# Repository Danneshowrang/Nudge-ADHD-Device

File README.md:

# Nudge-ADHD-Device

## What is it
Nudge is a haptic feedback device made to combat ADHD-related time blindness. It does this by stimulating the user ever 15 minutes with a haptic effect.

## Why I made this project
I made this project because I, as an indivdual with ADHD who is heavily affected by time blindness, have missed a lot of opportunities, deadlines, and dates. (just now I missed the Stasis deadline to recieve a 150-point discount)
I hope that with this device, I, and others with ADHD, can create an artificial perception of time and live life with less regrets. 

## Future Plans
In the future I want to expand this device to not only be a Time-blindness solution, but an entire ADHD multitool. 
This means adding additional features such as calendar reminders, built-in focus timers, date countdowns, and a user-interactive display.

## Pictures

## CAD Link
Here is the link to the Onshape!
https://cad.onshape.com/documents/210c189d286efe197b4a566f/w/a50a3c19759326f033c6858b/e/ea3b0ad6e4c0592fd1c20846?renderMode=0&uiState=6a46bb6c4d6ed321eca43a19

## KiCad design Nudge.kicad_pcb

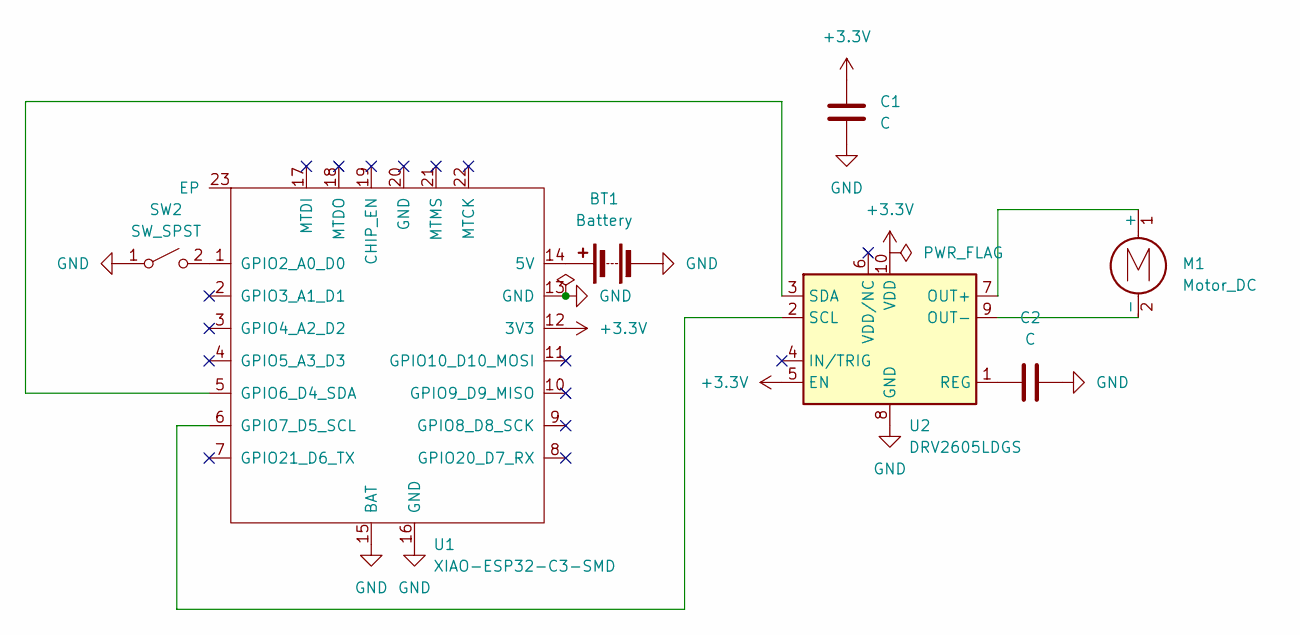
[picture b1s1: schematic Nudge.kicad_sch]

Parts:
BT1: Battery; SolderWire-0.5sqmm_1x02_P4.6mm_D0.9mm_OD2.1mm_Relief
C1, C2: C; C_0805_2012Metric
M1: Motor_DC; SolderWire-0.5sqmm_1x02_P4.6mm_D0.9mm_OD2.1mm_Relief
SW2: SW_SPST; SW_SPST_EVQP7A
U1: XIAO-ESP32-C3-SMD; MCU_Seeed_ESP32C3
U2: DRV2605LDGS; VSSOP-10_3x3mm_P0.5mm

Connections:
+3.3V: C1.1, U1.12 (3V3), U2.5 (EN), U2.10 (VDD)
GND: BT1.2 (-), C1.2, C2.2, SW2.1 (A), U1.13 (GND), U1.15 (BAT), U1.16 (GND), U2.8 (GND)
unnamed: BT1.1 (+), U1.14 (5V)
unnamed: M1.1 (+), U2.7 (OUT+)
unnamed: M1.2 (-), U2.9 (OUT-)
unnamed: SW2.2 (B), U1.1 (GPIO2_A0_D0)
unnamed: U1.5 (GPIO6_D4_SDA), U2.3 (SDA)
unnamed: U1.6 (GPIO7_D5_SCL), U2.2 (SCL)
unnamed: C2.1, U2.1 (REG)

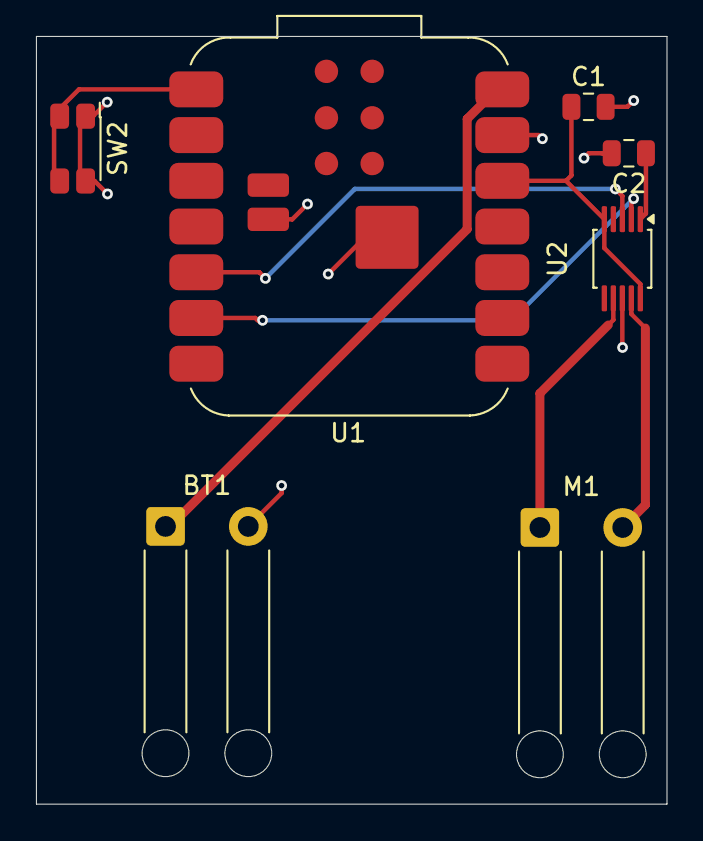
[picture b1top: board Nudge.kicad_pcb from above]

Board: 4 copper layers, 35.0 x 42.7 mm, 7 parts (0 on the bottom side), 9 nets.

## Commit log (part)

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2026-05-04 Rename Nudge.kicad_pro.kicad_pro to Nudge.kicad_pro
2026-05-04 Add Nudge.kicad_pcb file
2026-05-04 Enhance README with project details and images
    Expanded the README to include detailed project description, motivation, future plans, and images.
2026-05-04 Fix formatting in README sections
